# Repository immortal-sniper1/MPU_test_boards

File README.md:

# MPU_test_boards
 A repo where I have a few test boards for a few popular MPUs i intend to work more in the future.

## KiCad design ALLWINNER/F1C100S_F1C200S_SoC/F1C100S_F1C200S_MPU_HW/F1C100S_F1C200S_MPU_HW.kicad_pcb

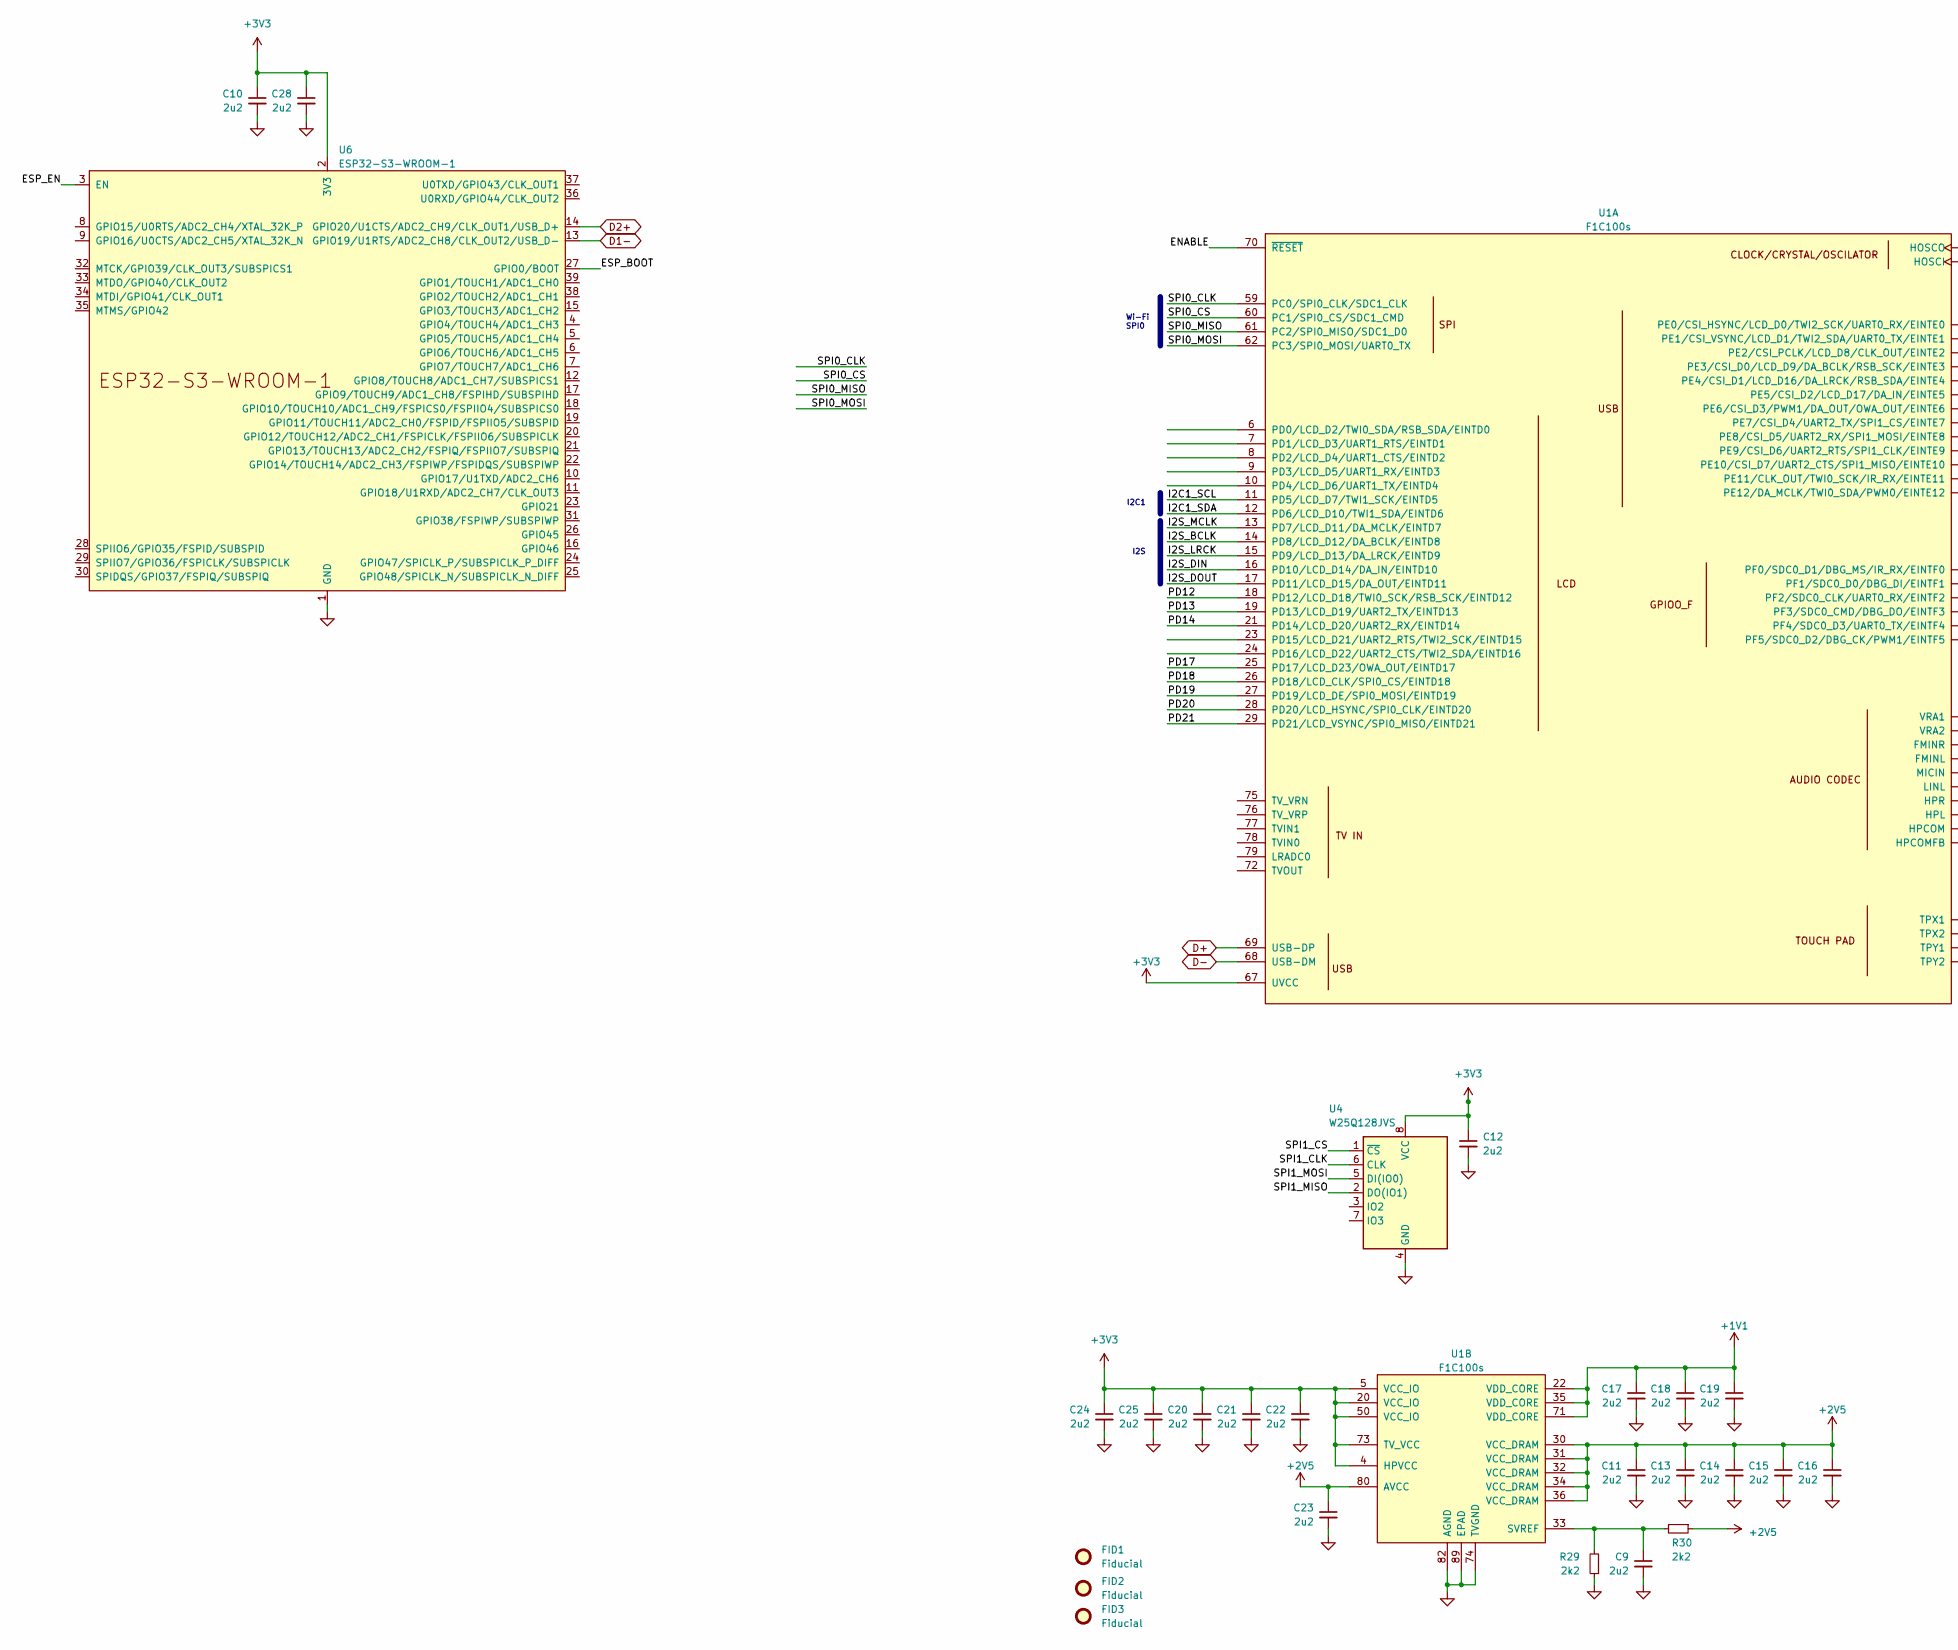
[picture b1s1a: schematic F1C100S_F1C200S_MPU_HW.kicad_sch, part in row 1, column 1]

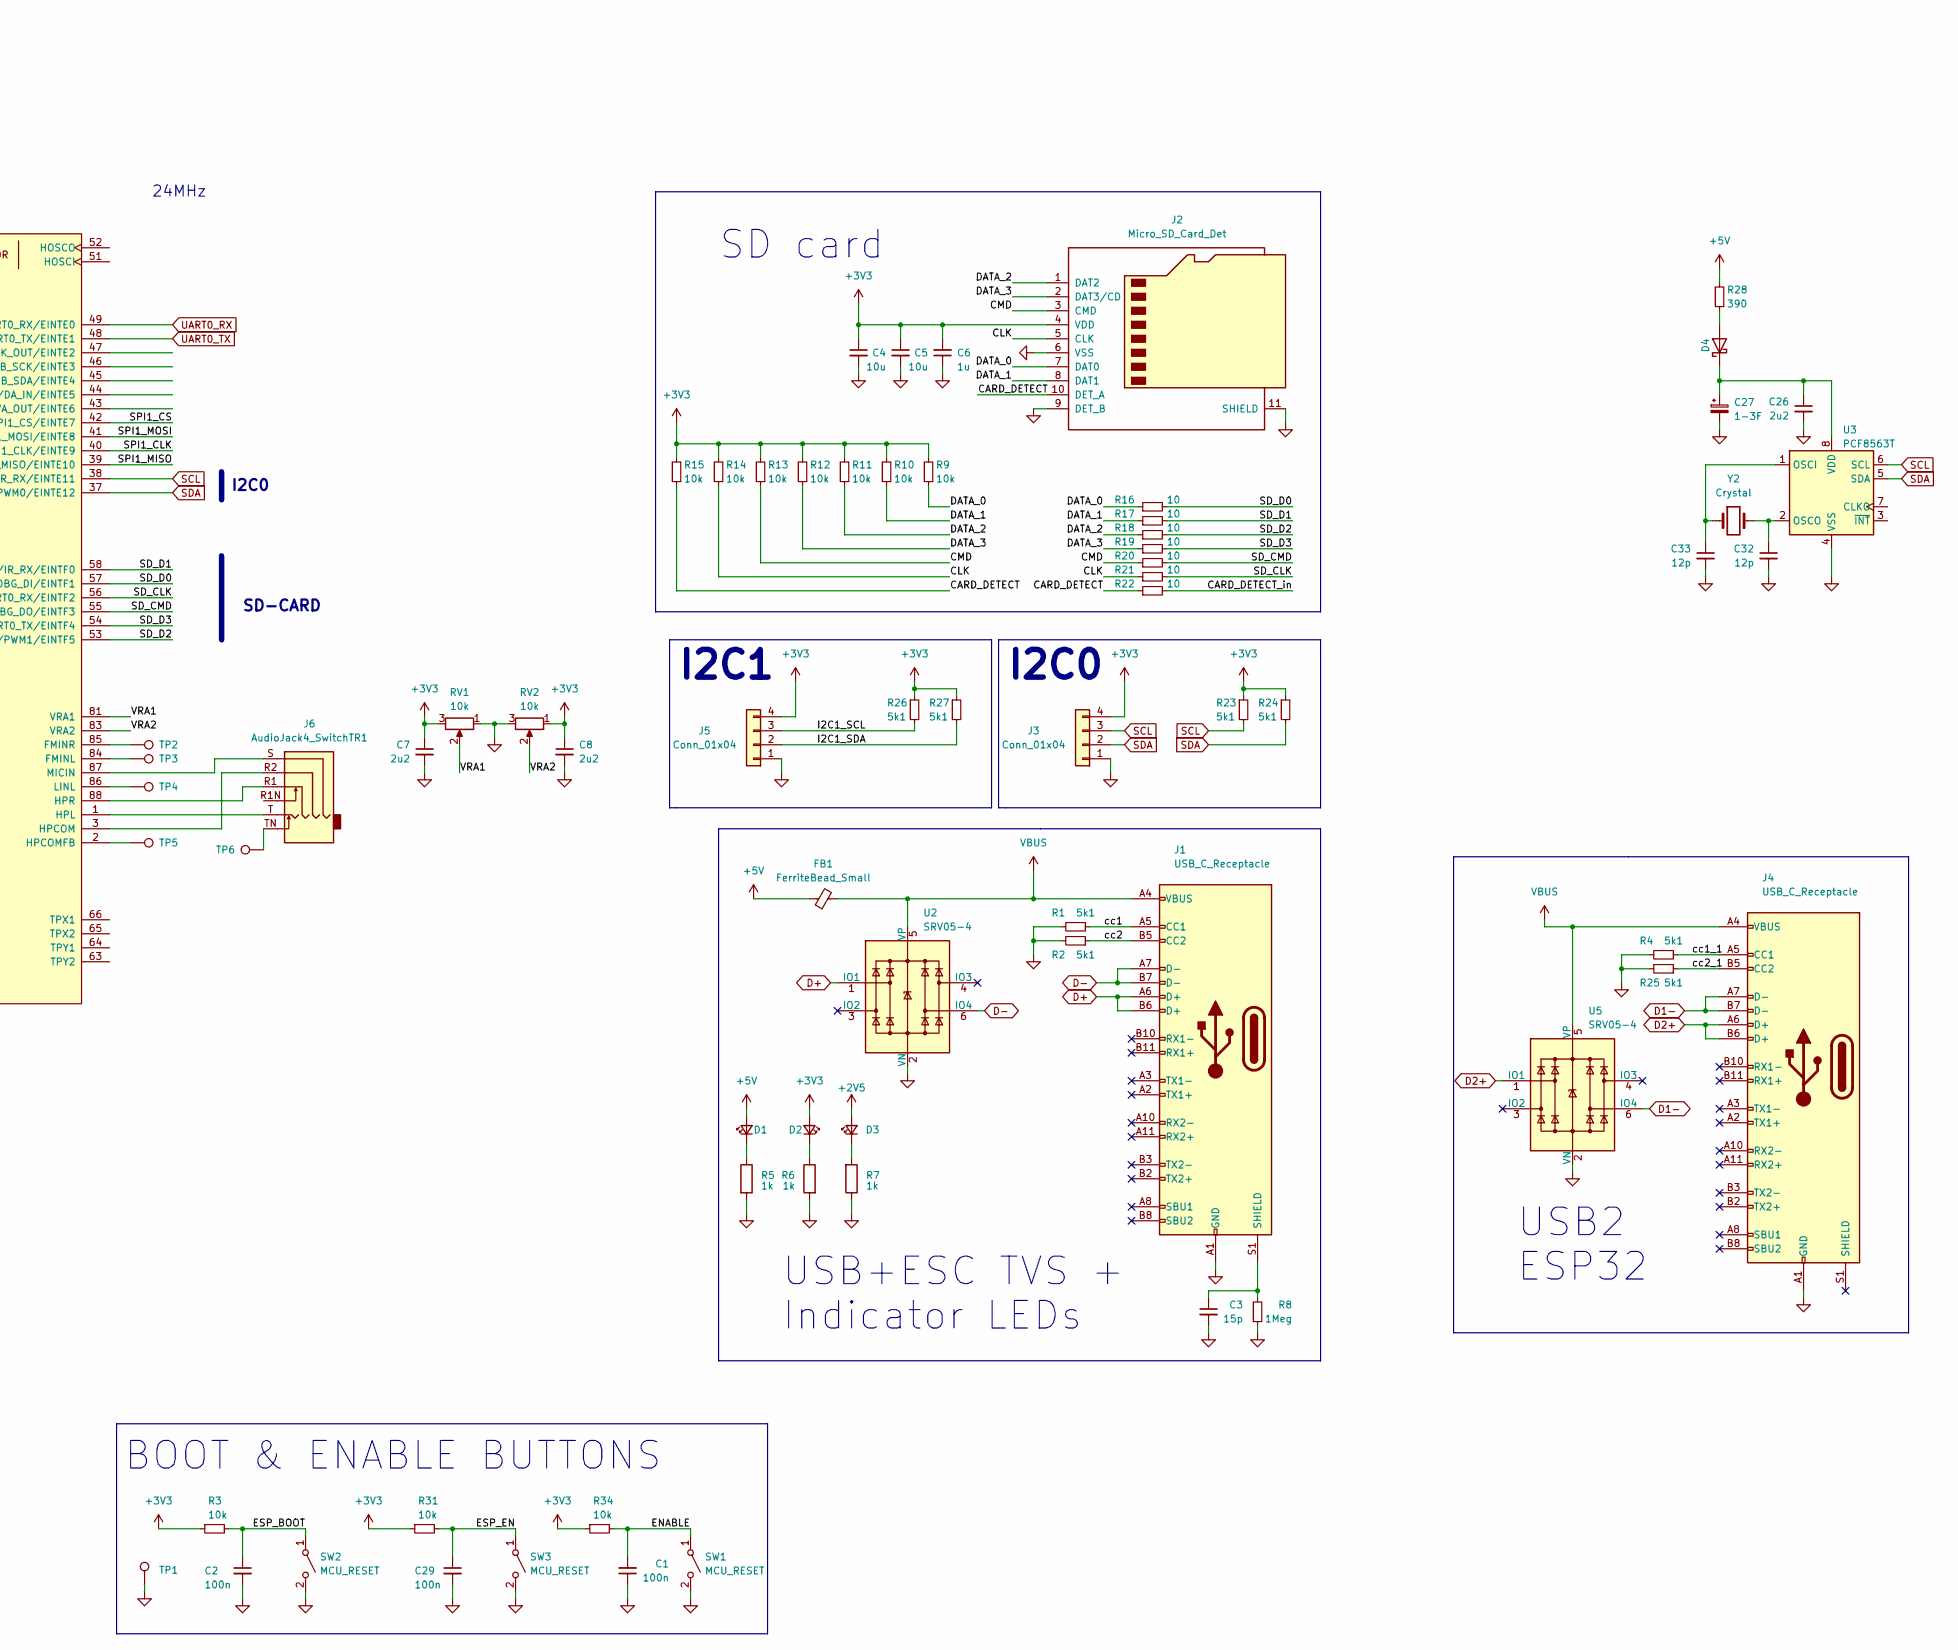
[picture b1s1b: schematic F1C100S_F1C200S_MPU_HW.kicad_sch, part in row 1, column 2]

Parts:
C1, C2, C29: 100n; C_0603_1608Metric_Pad1.08x0.95mm_HandSolder; LCSC C14663
C3: 15p; C_0603_1608Metric_Pad1.08x0.95mm_HandSolder; LCSC C1644
C4, C5: 10u; C_0603_1608Metric; LCSC C96446
C6: 1u; C_0603_1608Metric_Pad1.08x0.95mm_HandSolder; LCSC C15849
C7, C8, C9, C10, C11, C12, C13, C14, C15, C16, C17, C18, C19, C20, C21, C22, C23, C24, C25, C26, C28: 2u2; C_0402_1005Metric; LCSC C12530
C27: 1-3F
C32, C33: 12p; C_0402_1005Metric; LCSC C1547
D1, D2: green; LED_0805_2012Metric; LCSC C2297
D3: red; LED_0603_1608Metric; LCSC C2286
D4: D_Schottky; D_SMA_Handsoldering; LCSC C22452
FB1: FerriteBead_Small; R_0805_2012Metric; LCSC C1015
FID1: Fiducial; Fiducial_0.5mm_Mask1mm
FID2: Fiducial; KiCad-Logo2_5mm_SilkScreen
FID3: Fiducial; WEEE-Logo_4.2x6mm_SilkScreen
J1, J4: USB_C_Receptacle; USB_C_Receptacle_HRO_TYPE-C-31-M-12; LCSC C319148
J2: Micro_SD_Card_Det; microSD_HC_Molex_104031-0811; LCSC C585350
J3, J5: Conn_01x04; PinHeader_1x04_P2.54mm_Vertical
J6: AudioJack4_SwitchTR1; PJ-316A-6A; LCSC C128987
R1, R2, R4, R23, R24, R25, R26, R27: 5k1; R_0402_1005Metric; LCSC C25905
R3, R9, R10, R11, R12, R13, R14, R15, R31, R34: 10k; R_0402_1005Metric; LCSC C25744
R5, R6: 1k; R_0805_2012Metric; LCSC C17513
R7: 1k; R_0603_1608Metric; LCSC C21190
R8: 1Meg; R_0603_1608Metric_Pad0.98x0.95mm_HandSolder; LCSC C22935
R16, R17, R18, R19, R20, R21, R22: 10; R_0402_1005Metric; LCSC C25077
R28: 390; R_0603_1608Metric; LCSC C23151
R29, R30: 2k2; R_0402_1005Metric; LCSC C25879
RV1, RV2: 10k; Potentiometer_Bourns_3314J_Vertical; LCSC C36376
SW1, SW2, SW3: MCU_RESET; PTS526SK15SMTR2LFS; LCSC C318884
TP1, TP2, TP3, TP4, TP5, TP6: TestPoint; TestPoint_Pad_1.0x1.0mm
U1: F1C100s; QFN-88_EP_10x10_Pitch0.4mm; LCSC C2879851, C1511928
U2, U5: SRV05-4; SOT-23-6; LCSC C85364
U3: PCF8563T; SOIC-8_3.9x4.9mm_P1.27mm; LCSC C7440
U4: W25Q128JVS; SOIC-8_5.23x5.23mm_P1.27mm; LCSC C97521
U6: ESP32-S3-WROOM-1
Y2: Crystal; Crystal_SMD_3215-2Pin_3.2x1.5mm; LCSC C32346

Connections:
+1V1: C17.1, C18.1, C19.1, U1.22 (VDD_CORE), U1.35 (VDD_CORE), U1.71 (VDD_CORE)
+2V5: C11.1, C13.1, C14.1, C15.1, C16.1, C23.1, D3.2 (A), R30.1, U1.30 (VCC_DRAM), U1.31 (VCC_DRAM), U1.32 (VCC_DRAM), U1.34 (VCC_DRAM), U1.36 (VCC_DRAM), U1.80 (AVCC)
+3V3: C4.1, C5.1, C6.2, C7.1, C8.1, C10.1, C12.1, C20.1, C21.1, C22.1, C24.1, C25.1, C28.1, D2.2 (A), J2.4 (VDD), J3.4, J5.4, R3.1, R9.2, R10.2, R11.2, R12.2, R13.2, R14.2, R15.2, R23.1, R24.1, R26.1, R27.1, R31.1, R34.1, RV1.3, RV2.1, U1.4 (HPVCC), U1.5 (VCC_IO), U1.20 (VCC_IO), U1.50 (VCC_IO), U1.67 (UVCC), U1.73 (TV_VCC), U4.8 (VCC), U6.2 (3V3)
+5V: D1.2 (A), FB1.1, R28.2
/CARD_DETECT: J2.10 (DET_A), R15.1, R22.1
/CARD_DETECT_in: R22.2
/CLK: J2.5 (CLK), R14.1, R21.1
/CMD: J2.3 (CMD), R13.1, R20.1
/DATA_0: J2.7 (DAT0), R9.1, R16.1
/DATA_1: J2.8 (DAT1), R10.1, R17.1
/DATA_2: J2.1 (DAT2), R11.1, R18.1
/DATA_3: J2.2 (DAT3/CD), R12.1, R19.1
/ENABLE: C1.2, R34.2, SW1.1 (A), U1.70 (~RESET)
/ESP_BOOT: C2.1, R3.2, SW2.1 (A), U6.27 (GPIO0/BOOT)
/ESP_EN: C29.1, R31.2, SW3.1 (A), U6.3 (EN)
/I2C1_SCL: J5.3, R26.2, U1.11 (PD5/LCD_D7/TWI1_SCK/EINTD5)
/I2C1_SDA: J5.2, R27.2, U1.12 (PD6/LCD_D10/TWI1_SDA/EINTD6)
/I2S_BCLK: U1.14 (PD8/LCD_D12/DA_BCLK/EINTD8)
/I2S_DIN: U1.16 (PD10/LCD_D14/DA_IN/EINTD10)
/I2S_DOUT: U1.17 (PD11/LCD_D15/DA_OUT/EINTD11)
/I2S_LRCK: U1.15 (PD9/LCD_D13/DA_LRCK/EINTD9)
/I2S_MCLK: U1.13 (PD7/LCD_D11/DA_MCLK/EINTD7)
/PD12: U1.18 (PD12/LCD_D18/TWI0_SCK/RSB_SCK/EINTD12)
/PD13: U1.19 (PD13/LCD_D19/UART2_TX/EINTD13)
/PD14: U1.21 (PD14/LCD_D20/UART2_RX/EINTD14)
/PD17: U1.25 (PD17/LCD_D23/OWA_OUT/EINTD17)
/PD18: U1.26 (PD18/LCD_CLK/SPI0_CS/EINTD18)
/PD19: U1.27 (PD19/LCD_DE/SPI0_MOSI/EINTD19)
/PD20: U1.28 (PD20/LCD_HSYNC/SPI0_CLK/EINTD20)
/PD21: U1.29 (PD21/LCD_VSYNC/SPI0_MISO/EINTD21)
/SD_CLK: R21.2, U1.56 (PF2/SDC0_CLK/UART0_RX/EINTF2)
/SD_CMD: R20.2, U1.55 (PF3/SDC0_CMD/DBG_DO/EINTF3)
/SD_D0: R16.2, U1.57 (PF1/SDC0_D0/DBG_DI/EINTF1)
/SD_D1: R17.2, U1.58 (PF0/SDC0_D1/DBG_MS/IR_RX/EINTF0)
/SD_D2: R18.2, U1.53 (PF5/SDC0_D2/DBG_CK/PWM1/EINTF5)
/SD_D3: R19.2, U1.54 (PF4/SDC0_D3/UART0_TX/EINTF4)
/SPI0_CLK: U1.59 (PC0/SPI0_CLK/SDC1_CLK)
/SPI0_CS: U1.60 (PC1/SPI0_CS/SDC1_CMD)
/SPI0_MISO: U1.61 (PC2/SPI0_MISO/SDC1_D0)
/SPI0_MOSI: U1.62 (PC3/SPI0_MOSI/UART0_TX)
/SPI1_CLK: U1.40 (PE9/CSI_D6/UART2_RTS/SPI1_CLK/EINTE9), U4.6 (CLK)
/SPI1_CS: U1.42 (PE7/CSI_D4/UART2_TX/SPI1_CS/EINTE7), U4.1 (~CS)
/SPI1_MISO: U1.39 (PE10/CSI_D7/UART2_CTS/SPI1_MISO/EINTE10), U4.2 (DO(IO1))
/SPI1_MOSI: U1.41 (PE8/CSI_D5/UART2_RX/SPI1_MOSI/EINTE8), U4.5 (DI(IO0))
/VRA1: RV1.2, U1.81 (VRA1)
/VRA2: RV2.2, U1.83 (VRA2)
/cc1: J1.A5 (CC1), R1.1
/cc1_1: J4.A5 (CC1), R4.1
/cc2: J1.B5 (CC2), R2.1
/cc2_1: J4.B5 (CC2), R25.1
D1-: J4.A7 (D-), J4.B7 (D-), U5.6 (IO4), U6.13 (GPIO19/U1RTS/ADC2_CH8/CLK_OUT2/USB_D-)
D2+: J4.A6 (D+), J4.B6 (D+), U5.1 (IO1), U6.14 (GPIO20/U1CTS/ADC2_CH9/CLK_OUT1/USB_D+)
D+: J1.A6 (D+), J1.B6 (D+), U1.69 (USB-DP), U2.1 (IO1)
D-: J1.A7 (D-), J1.B7 (D-), U1.68 (USB-DM), U2.6 (IO4)
GND: C1.1, C2.2, C3.2, C4.2, C5.2, C6.1, C7.2, C8.2, C9.2, C10.2, C11.2, C12.2, C13.2, C14.2, C15.2, C16.2, C17.2, C18.2, C19.2, C20.2, C21.2, C22.2, C23.2, C24.2, C25.2, C26.2, C28.2, C29.2, C32.2, C33.2, J1.A1 (GND), J1.A12 (GND), J1.B1 (GND), J1.B12 (GND), J2.6 (VSS), J2.9 (DET_B), J2.11 (SHIELD), J3.1, J4.A1 (GND), J4.A12 (GND), J4.B1 (GND), J4.B12 (GND), J5.1, R1.2, R2.2, R4.2, R5.2, R6.2, R7.1, R8.1, R25.2, R29.1, RV1.1, RV2.3, SW1.2 (B), SW2.2 (B), SW3.2 (B), U1.74 (TVGND), U1.82 (AGND), U1.89 (EPAD), U2.2 (VN), U3.4 (VSS), U4.4 (GND), U5.2 (VN), U6.1 (GND), U6.40 (GND), U6.41 (GND)
unnamed: D1.1 (K), R5.1
unnamed: D2.1 (K), R6.1
unnamed: D3.1 (K), R7.2
unnamed: D4.2 (A), R28.1
unnamed: C26.1, D4.1 (K), U3.8 (VDD)
unnamed: C3.1, J1.S1 (SHIELD), R8.2
unnamed: J6.TN, TP6.1
unnamed: TP3.1, U1.84 (FMINL)
unnamed: TP2.1, U1.85 (FMINR)
unnamed: J6.R2, U1.3 (HPCOM)
unnamed: TP5.1, U1.2 (HPCOMFB)
unnamed: J6.T, U1.1 (HPL)
unnamed: J6.R1, U1.88 (HPR)
unnamed: TP4.1, U1.86 (LINL)
unnamed: J6.S, U1.87 (MICIN)
unnamed: C9.1, R29.2, R30.2, U1.33 (SVREF)
unnamed: C33.1, U3.1 (OSCI), Y2.1
unnamed: C32.1, U3.2 (OSCO), Y2.2
SCL: J3.3, R23.2, U1.38 (PE11/CLK_OUT/TWI0_SCK/IR_RX/EINTE11), U3.6 (SCL)
SDA: J3.2, R24.2, U1.37 (PE12/DA_MCLK/TWI0_SDA/PWM0/EINTE12), U3.5 (SDA)
UART0_RX: U1.49 (PE0/CSI_HSYNC/LCD_D0/TWI2_SCK/UART0_RX/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)
UART0_TX: U1.48 (PE1/CSI_VSYNC/LCD_D1/TWI2_SDA/UART0_TX/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)
VBUS: FB1.2, J1.A4 (VBUS), J1.A9 (VBUS), J1.B4 (VBUS), J1.B9 (VBUS), J4.A4 (VBUS), J4.A9 (VBUS), J4.B4 (VBUS), J4.B9 (VBUS), U2.5 (VP), U5.5 (VP)

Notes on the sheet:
USB+ESC TVS + Indicator LEDs
BOOT & ENABLE BUTTONS
24MHz
USB2 ESP32
SD card
I2C0
I2C1
Wi-Fi SPI0
SD-CARD
I2S

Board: 4 copper layers, 88 parts (0 on the bottom side), 53 nets, no tracks yet.
